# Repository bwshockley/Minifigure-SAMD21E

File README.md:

# Minifigure-SAMD21E
SAMD21E based Minifigure shaped development board.

## About
This circuit board was designed as a fun project for a SAMD21E microcontroller based development board.  The circuit design follows the recommended design from the SAMD Datasheet - including section 39. Schematic Checklist.  The USB protection may be overkill, but it is complete.  I made this just for fun - I am not going to provide any special support, but always welcome recommendations, suggestions, and ideas for improvements.  You are free to take it and run with it, but do not sell this design.

Order boards here:
Board 1: Stand alone - haven't tested, but should soon. [OSHPark](https://oshpark.com/shared_projects/Wh7NwFnv)

Board 2: This does not have a native USB or programming port - I am developing a backpack for it.  Will share backpack. [OSHPark](https://oshpark.com/shared_projects/W2bUXtFr)

MINI SAM TQFP SIMPLE - This version is more friendly to hand soldering with a TQFP SAMD21E chip.  USB protection and filtering removed, reset debounce removed.  [OSHPARK](https://oshpark.com/shared_projects/yFTXsDW0)

MINI SAM TQFP 1.27 SIMPLE - This version retains the TQFP SAMD21E chip, but on the back instead of the tiny 8-pin connector - I've replaced it with a 1.27mm pitch SMT connector.  Still trying to retain a "backpack" idea for add-on boards.  [OSHPARK](https://oshpark.com/shared_projects/vt6FGicv)

MINI SAM TQFP 2.54 BB (BreadBoard or Protoboard) - This version changes the rear once more to a 2.54mm pitch SMT setup for a protoboard friendly design. [OSHPARK](https://oshpark.com/shared_projects/SMD5UkUu)

Mini SAM - Protoboard - TQFP - 2017-01-17-00 - This version is similar to the other BB version, but has some refinements to layout and includes options for the onboard LED (Basic LED or the WS2812B), a plain button, and other enhancements.  [OSHPARK](https://oshpark.com/shared_projects/IhRoccbe)

Mini SAM 2017/01-001 - Latest version with minor changes and enhancements.  Once this version passes validation and verification, I will most likely archive other versions.  Details on [OSHPARK](https://oshpark.com/shared_projects/dv4tvRPH) and [here](https://github.com/bwshockley/Minifigure-SAMD21E/tree/master/board/2017/01).

----------------------------------

## Etc
The board passes all DRC for OSHPark manufacturing and should pass for most other manufacturers as well - I kept most routes, vias, etc larger than minimums and allowed plenty of space where I could.  I have tested many of these boards and all features work as designed.

## BOM
*The BOM listed at mouser is for the Mini SAM - Protoboard - TQFP - 2017-01-17-004 board.  It is a good place to start, but keep in mind you may want to change or leave out items you don't want.*

The schematic has all items listed and values and should be easily sourced.  Additionally, I have setup a [project on mouser.com that can be found here.](http://www.mouser.com/ProjectManager/ProjectDetail.aspx?AccessID=328cc4307e)  The BOM through mouser is roughly 12 USD at this time (Oct 2016).  It does not include the WS8212B 3535 LED - these can be sourced from [Adafruit](https://www.adafruit.com/products/2659) or eBay among others.  The LED does not need to be populated for the board to function, but it is fun.

## Firmware
I plan on trying to implement both Arduino and possibly Micropython on this board, but need some significant help with this.  I will update as I can.

In order to test my prototype board, I loaded the Arduino Zero bootloader, but changes the PortA pin 14 for PostA Pin 27.  Nothing else is fucntional yet - it was a bad hack to get access to the WS2812 LED for the time being and to prove to myself the board will work in theory.

(01-20-2017) FIRMWARE has been updated and almost complete.  I'm working through the last bit of verification and validation now.  Firmware and Arduino files are available in the arduino folder.  In order to burn the bootloader, the Atmel SAM-BA In-System Programmer must be installed first.

## License
Hardware - CC BY-NC 4.0 - See License file.

Software
Copyright (c) 2017 Benjamin Shockley

Permission is hereby granted, free of charge, to any person obtaining a copy
of this software and associated documentation files (the "Software"), to deal
in the Software without restriction, including without limitation the rights
to use, copy, modify, merge, publish, distribute, sublicense, and/or sell
copies of the Software, and to permit persons to whom the Software is
furnished to do so, subject to the following conditions:

The above copyright notice and this permission notice shall be included in all
copies or substantial portions of the Software.

THE SOFTWARE IS PROVIDED "AS IS", WITHOUT WARRANTY OF ANY KIND, EXPRESS OR
IMPLIED, INCLUDING BUT NOT LIMITED TO THE WARRANTIES OF MERCHANTABILITY,
FITNESS FOR A PARTICULAR PURPOSE AND NONINFRINGEMENT. IN NO EVENT SHALL THE
AUTHORS OR COPYRIGHT HOLDERS BE LIABLE FOR ANY CLAIM, DAMAGES OR OTHER
LIABILITY, WHETHER IN AN ACTION OF CONTRACT, TORT OR OTHERWISE, ARISING FROM,
OUT OF OR IN CONNECTION WITH THE SOFTWARE OR THE USE OR OTHER DEALINGS IN THE
SOFTWARE.

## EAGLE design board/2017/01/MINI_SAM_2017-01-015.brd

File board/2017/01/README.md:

##Board 2017/01-002

This is a LEGO Minifigure sized development board using an Atmel SAMD21E 32-Bit ARM chip. I basically followed the recommended layout/setup from the SAMD21 spec sheets.

Included on Mini SAM is a WS2812B LED (STATUS) connected to PIN 27, a 0603 LED (L) connected to PIN 15, a reset button (SW1) with circuitry per datasheet connected to !RESET, and a user programmable button (SW1) that is active HIGH connected to PIN 28. The 0603 LED is connected in series with a 1Kohm resistor, part of R1, and care should be taken when selecting an 0603 LED such that at a supply of 3.3V, no more than 5mA is required.

Programming port (PROG) is a basic 10-pin SWD for ARM based processors, which is a 2x5 1.27mm pitch connector. The SWD line is pulled up with a 1Kohm resistor, part of R1.

The SDA/SCL pins are pulled high with 4.7KOhm resistors, R2, per SDA/SCL recommendations.

The voltage regulator is an MCP1700 (IC1) which is rated at 250mA at 3.3V. Plenty of current for the SAMD21E and a few other accessories such as the WS2812B.

This version has SMT layout for two single row 2.54mm pitch headers on the back. It is designed to be protoboard friendly and when populated the headers are the same width as a DIL package (7.62mm or .3") and span the center of a protoboard.

PINs 27 and 28 are not connected to the headers - due to lack of space - but instead have two pads near the bottom of the board. Reminder: PIN 27 is connected to the on-board WS2812B and PIN 28 is connected to the on-board BUTTON.

The AREF PIN - PIN AREF - has a pair of decoupling/filtering capacitors (C6, C11).

The micro-USB connector has an RC filter (R6, C13) between the case/shield of the connector and GND. If left un-populated the case/shield is an open circuit - which is the next best option. Also included is space for a USBLC6-2 (IC2) ESD protection circuit. You can bypass it by jumping PAD 1 to 6, and PAD 3 to 4, leaving the middle two PADs alone of the layout for IC2.

I have put together a sample BOM via Mouser.com which I’m including here. It can be used as a reference. Items that do not need to be populated to work: SW2812B 3535 LED, 0603 LED, SW2 (BUTTON). The SW2812B is not in the Mouser BOM - due to lack of parts. I would suggest not purchasing the 2.54mm pitch SMT male headers from Mouser, as you can find this much cheaper elsewhere. Mini SAM requires (2) 11-PIN headers. I suggest buying breakaway headers in 25-50 PIN lengths.

Arduino FIRMWARE/BOOTLOADER is complete, but I’m still testing all functions. So far all PINs work in digital setup and all analog PINs work accordingly. ANALOG and special function pins (MOSI, SDA, SCK, etc) can be accessed in Arduino by their name.

##Board 2017/01-010

This is a LEGO Minifigure sized development board using an Atmel SAMD21E 32-Bit ARM chip.  I basically followed the recommended layout/setup from the SAMD21 spec sheets.

Included on Mini SAM is a WS2812B LED pad connected to PIN 27, a 0603 LED connected to PIN 15, a reset button with support components per the datasheet, and a generic button that is active HIGH on PIN 28. The 0603 LED is connected in series with a 1Kohm resistor, part of R1, and care should be taken when selecting an 0603 LED such that at a supply of 3.3V, no more than 5mA is required.

Programming port is a standard10-pin SWD for ARM based processors, which is a 2x5 1.27mm pitch connector.  The SWD line is pulled up with a 1Kohm resistor, part of R1.  In the BOM, either purchase the 2x5 straight pin connector OR the 2x5 POGO connector and do not populate board.

The SDA/SCL pins are pulled high with 4.7KOhm resistors, R2, per SDA/SCL recommendations.

The voltage regulator is an AP2112K-3.3V which is rated at 600mA at 3.3V.  Plenty of current for the SAMD21E and a few other accessories such as the WS2812B.

This version has SMT layout for two single row 2.54mm pitch headers on the back.  It is designed to be protoboard friendly and when populated the headers are the same width as a DIL package (7.62mm or .3") and span the center of a protoboard.

PINs 27 and 28 are not connected to headers - due to lack of space - but instead have two pads near the bottom of the board.  PIN 27 is connected to the on-board WS2812B.  PIN 28 is connected to the on-board BUTTON.

The Analog Reference (PIN AREF) - has a pair of decoupling/filtering capacitors.

The micro-USB connector has an RC filter between the case/shield of the connector and GND.  If R6 and C13 are left un-populated the case/shield is an open circuit - which is the next best option.  Also included is space for a PRTR5V0U2X ESD protection circuit on USB Data lines.  This may also be left un-populated and USB will function normally.

I have put together a sample BOM via Mouser.com which I'm including here.  It can be used as a reference.  Optional, but highly recommended components: SW2812B 3535 LED, 0603 LED, SW2 (BUTTON), R4, R5, R6, C13, and PRTR5V0U2X.  R1 is for the 0603 LED and SWCLK - If not populating the 0603 LED this *may* be left un-populated as well and programming via SWD should still work as I've seen other boards without the 1Kohm resistor on SWCLK.  R2 is the 4.7Kohm pull-up resistor pair for SDA/SCL.  Many breakout boards using chips that run off SDA/SCL typically come with the 4.7Kohm pull-up resistor pair included - as such it may not be needed on Mini SAM - but it is included for ease of future components.  Please review the schematic for additional details and be aware that the BOM on Mouser.com may be out of date.  *The SW2812B is not in the Mouser BOM - due to lack of parts.*

[Mouser BOM](http://www.mouser.com/ProjectManager/ProjectDetail.aspx?AccessID=fc486f90dc)

I would suggest not purchasing the 2.54mm pitch SMT male headers from Mouser, as you can find this much cheaper elsewhere.  The best I could find on Mouser is (2) 5-Pin and (2) 6-Pin headers.  Mini SAM requires (2) 11-PIN headers.  I suggest buying breakaway headers in 25-50 PIN lengths.

Arduino FIRMWARE/BOOTLOADER is complete, but I'm still testing all functions.  So far all PINs work in digital setup and all analog PINs work accordingly.  ANALOG and special function pins (MOSI, SDA, SCK, etc) can be accessed in Arduino by their name.

Please check my Github for the latest design files and bootloade/firmware.

More details can be found on [Github](https://github.com/bwshockley/Minifigure-SAMD21E)

##Board 2017/01-012
Same as 2017/01-010 with minor cosmetic changes.

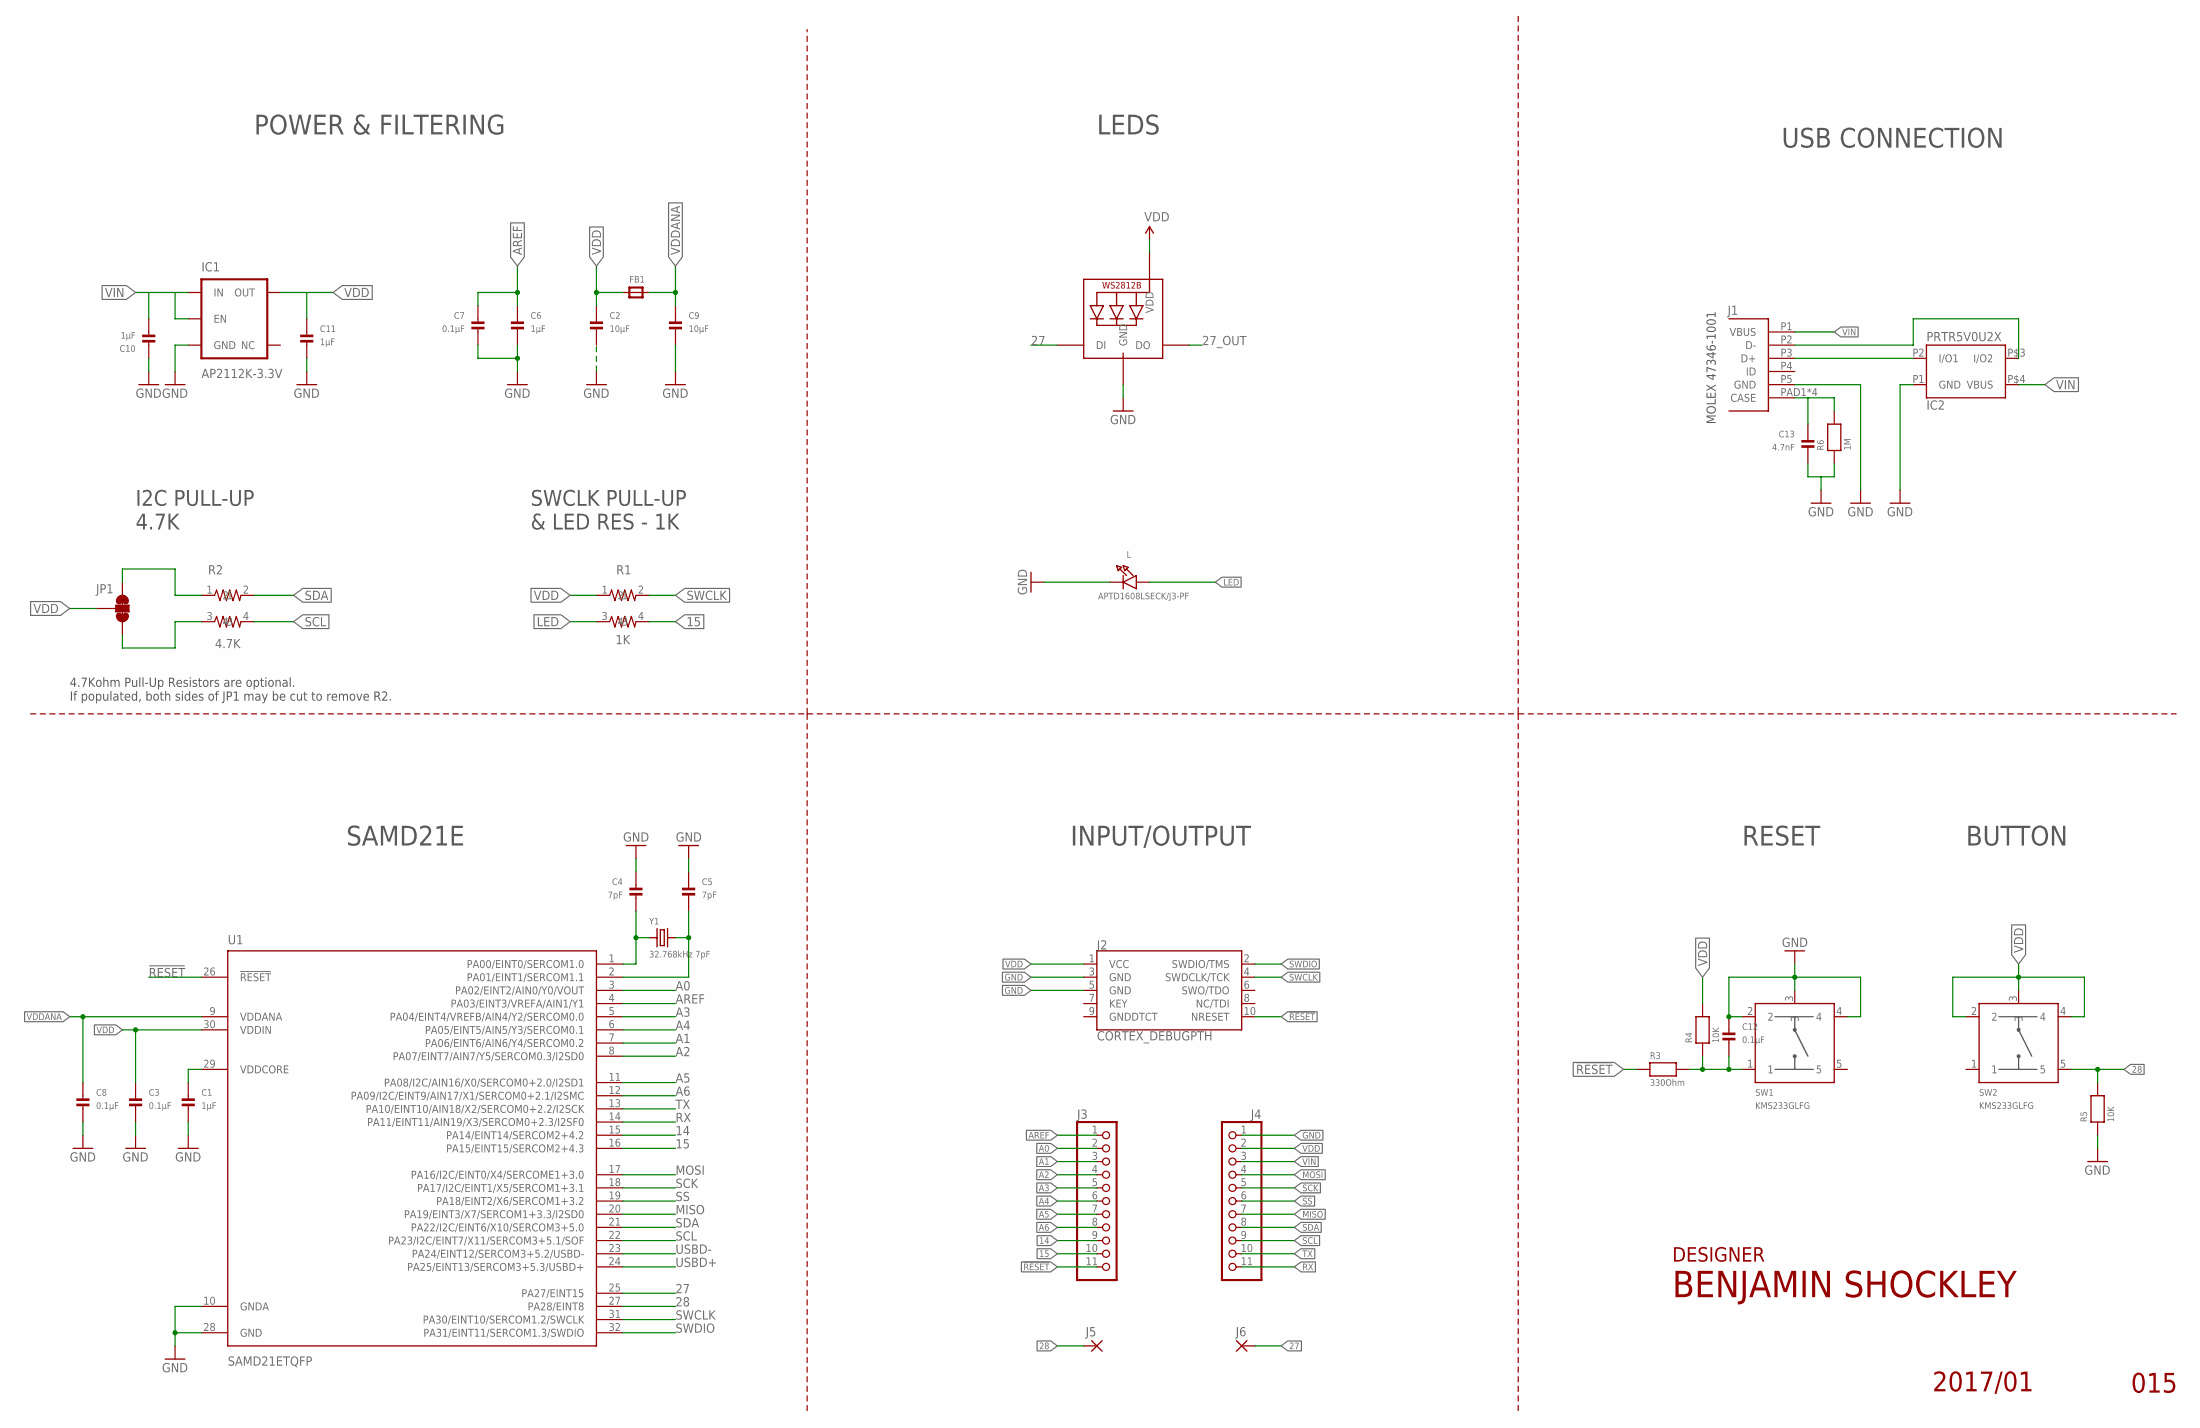
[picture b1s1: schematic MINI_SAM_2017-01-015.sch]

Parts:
C1, C6, C10, C11: 1µF; _0805MP
C2, C9: 10µF; _0805MP
C3, C7, C8, C12: 0.1µF; _0805MP
C4, C5: 7pF; _0805MP
C13: 4.7nF; _0805MP
FB1: FERRITE_0805MP; _0805MP
IC1: AP2112K-3.3V; SOT23-5
IC2: PRTR5V0U2X; SOT143B_REFLOW
J1: MOLEX_47346-100147346; MOLEX_47346-1001
J2: CORTEX_DEBUGPTH; 2X5-PTH-1.27MM
J3, J4: PINHD-1X111X11_SMT; 1X11_SMT
J5, J6: FR11_PAD2MMX1MM; SMD2MMX1MM
JP1: JUMPER-SMT_3_2-NC_TRACE_NO-SILK; SMT-JUMPER_3_2-NC_TRACE_NO-SILK
L: APTD1608LSECK/J3-PF; CHIPLED_0603_NOOUTLINE
R1: 1K; RESISTOR_ARRAY_0606
R2: 4.7K; RESISTOR_ARRAY_0606
R3: 330Ohm; _0805MP
R4, R5: 10K; _0805MP
R6: 1M; _0805MP
STATUS: WS2812B3535; LED3535
SW1, SW2: KMS233GLFG; KMS_SWITCH
U1: SAMD21ETQFP; TQFP32-08
Y1: 32.768kHz 7pF; _0805MP

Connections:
14: J3.9, U1.15 (PA14/EINT14/SERCOM2+4.2)
15: J3.10, R1.4, U1.16 (PA15/EINT15/SERCOM2+4.3)
27: J6.P$1, STATUS.1 (DI), U1.25 (PA27/EINT15)
27_OUT: STATUS.3 (DO)
28: J5.P$1, R5.2, SW2.5, U1.27 (PA28/EINT8)
!RESET: J2.10 (NRESET), J3.11, R3.1, U1.26 (!RESET)
A0: J3.2, U1.3 (PA02/EINT2/AIN0/Y0/VOUT)
A1: J3.3, U1.7 (PA06/EINT6/AIN6/Y4/SERCOM0.2)
A2: J3.4, U1.8 (PA07/EINT7/AIN7/Y5/SERCOM0.3/I2SD0)
A3: J3.5, U1.5 (PA04/EINT4/VREFB/AIN4/Y2/SERCOM0.0)
A4: J3.6, U1.6 (PA05/EINT5/AIN5/Y3/SERCOM0.1)
A5: J3.7, U1.11 (PA08/I2C/AIN16/X0/SERCOM0+2.0/I2SD1)
A6: J3.8, U1.12 (PA09/I2C/EINT9/AIN17/X1/SERCOM0+2.1/I2S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)
AREF: C6.1, C7.1, J3.1, U1.4 (PA03/EINT3/VREFA/AIN1/Y1)
GND: C1.2, C2.2, C3.2, C4.1, C5.1, C6.2, C7.2, C8.2, C9.2, C10.1, C11.2, C12.1, C13.2, IC1.2 (GND), IC2.P1 (GND), J1.P5 (GND), J2.3 (GND), J2.5 (GND), J4.1, L.C, R5.1, R6.1, STATUS.4 (GND), SW1.2, SW1.3, SW1.4, U1.10 (GNDA), U1.28 (GND)
LED: L.A, R1.3
MISO: J4.7, U1.20 (PA19/EINT3/X7/SERCOM1+3.3/I2SD0)
MOSI: J4.4, U1.17 (PA16/I2C/EINT0/X4/SERCOME1+3.0)
unnamed: C4.2, U1.1 (PA00/EINT0/SERCOM1.0), Y1.1
unnamed: C13.1, J1.PAD1 (CASE), J1.PAD2 (CASE), J1.PAD3 (CASE), J1.PAD4 (CASE), R6.2
unnamed: JP1.1, R2.1
unnamed: C12.2, R3.2, R4.1, SW1.1
unnamed: C5.2, U1.2 (PA01/EINT1/SERCOM1.1), Y1.2
unnamed: JP1.3, R2.3
unnamed: C1.1, U1.29 (VDDCORE)
RX: J4.11, U1.14 (PA11/EINT11/AIN19/X3/SERCOM0+2.3/I2SF0)
SCK: J4.5, U1.18 (PA17/I2C/EINT1/X5/SERCOM1+3.1)
SCL: J4.9, R2.4, U1.22 (PA23/I2C/EINT7/X11/SERCOM3+5.1/SOF)
SDA: J4.8, R2.2, U1.21 (PA22/I2C/EINT6/X10/SERCOM3+5.0)
SS: J4.6, U1.19 (PA18/EINT2/X6/SERCOM1+3.2)
SWCLK: J2.4 (SWDCLK/TCK), R1.2, U1.31 (PA30/EINT10/SERCOM1.2/SWCLK)
SWDIO: J2.2 (SWDIO/TMS), U1.32 (PA31/EINT11/SERCOM1.3/SWDIO)
TX: J4.10, U1.13 (PA10/EINT10/AIN18/X2/SERCOM0+2.2/I2SCK)
USBD+: IC2.P2 (I/O1), J1.P3 (D+), U1.24 (PA25/EINT13/SERCOM3+5.3/USBD+)
USBD-: IC2.P$3 (I/O2), J1.P2 (D-), U1.23 (PA24/EINT12/SERCOM3+5.2/USBD-)
VDD: C2.1, C3.1, C11.1, FB1.1, IC1.5 (OUT), J2.1 (VCC), J4.2, JP1.2, R1.1, R4.2, STATUS.2 (VDD), SW2.2, SW2.3, SW2.4, U1.30 (VDDIN)
VDDANA: C8.1, C9.1, FB1.2, U1.9 (VDDANA)
VIN: C10.2, IC1.1 (IN), IC1.3 (EN), IC2.P$4 (VBUS), J1.P1 (VBUS), J4.3

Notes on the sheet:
INPUT/OUTPUT
RESET
POWER & FILTERING
SAMD21E
LEDS
USB CONNECTION
I2C PULL-UP 4.7K
MOLEX 47346-1001
BUTTON
SWCLK PULL-UP & LED RES - 1K
DESIGNER
4.7Kohm Pull-Up Resistors are optional. If populated, both sides of JP1 may be cut to remove R2.

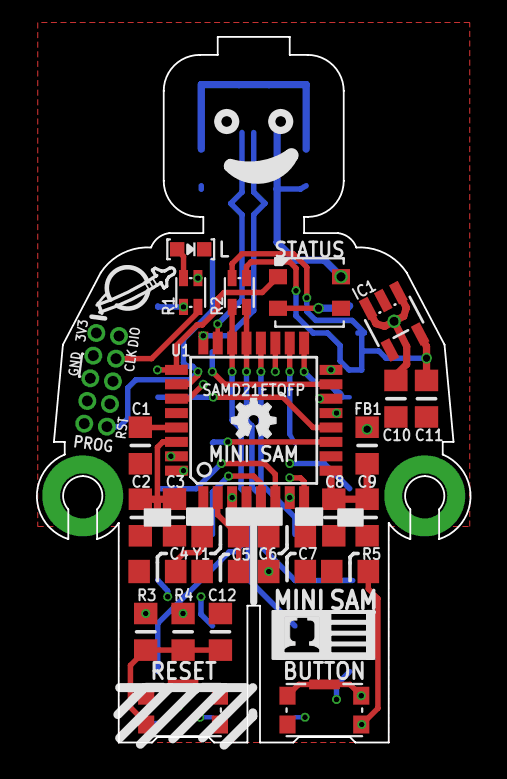
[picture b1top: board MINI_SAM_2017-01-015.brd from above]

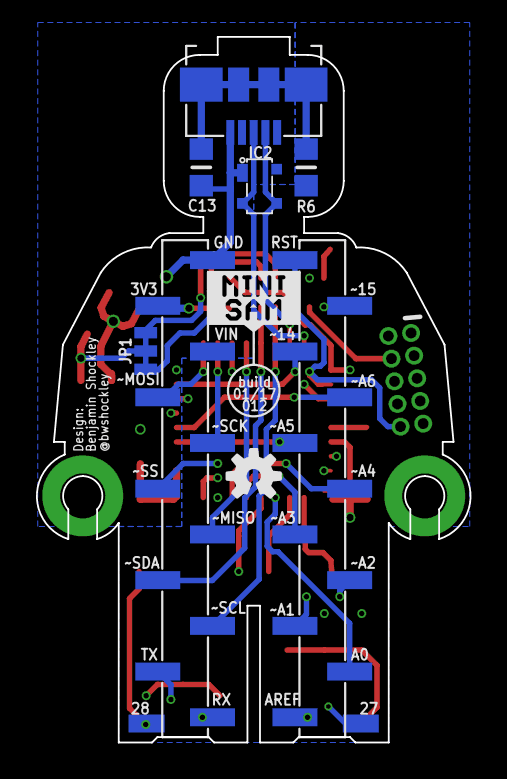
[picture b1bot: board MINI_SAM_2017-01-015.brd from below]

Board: 4 copper layers, 24.1 x 39.2 mm, 37 parts (10 on the bottom side), 37 nets.

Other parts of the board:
U$1: OSHW-LOGO-MINI
U$3: OSHW-LOGO-S

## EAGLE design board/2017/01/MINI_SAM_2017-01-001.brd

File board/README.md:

#EAGLE Files
At this time I only have EAGLE files for the Minifigure Board.  If someone wants to convert them to KiCAD, I'd be happy to add those files to the repository.

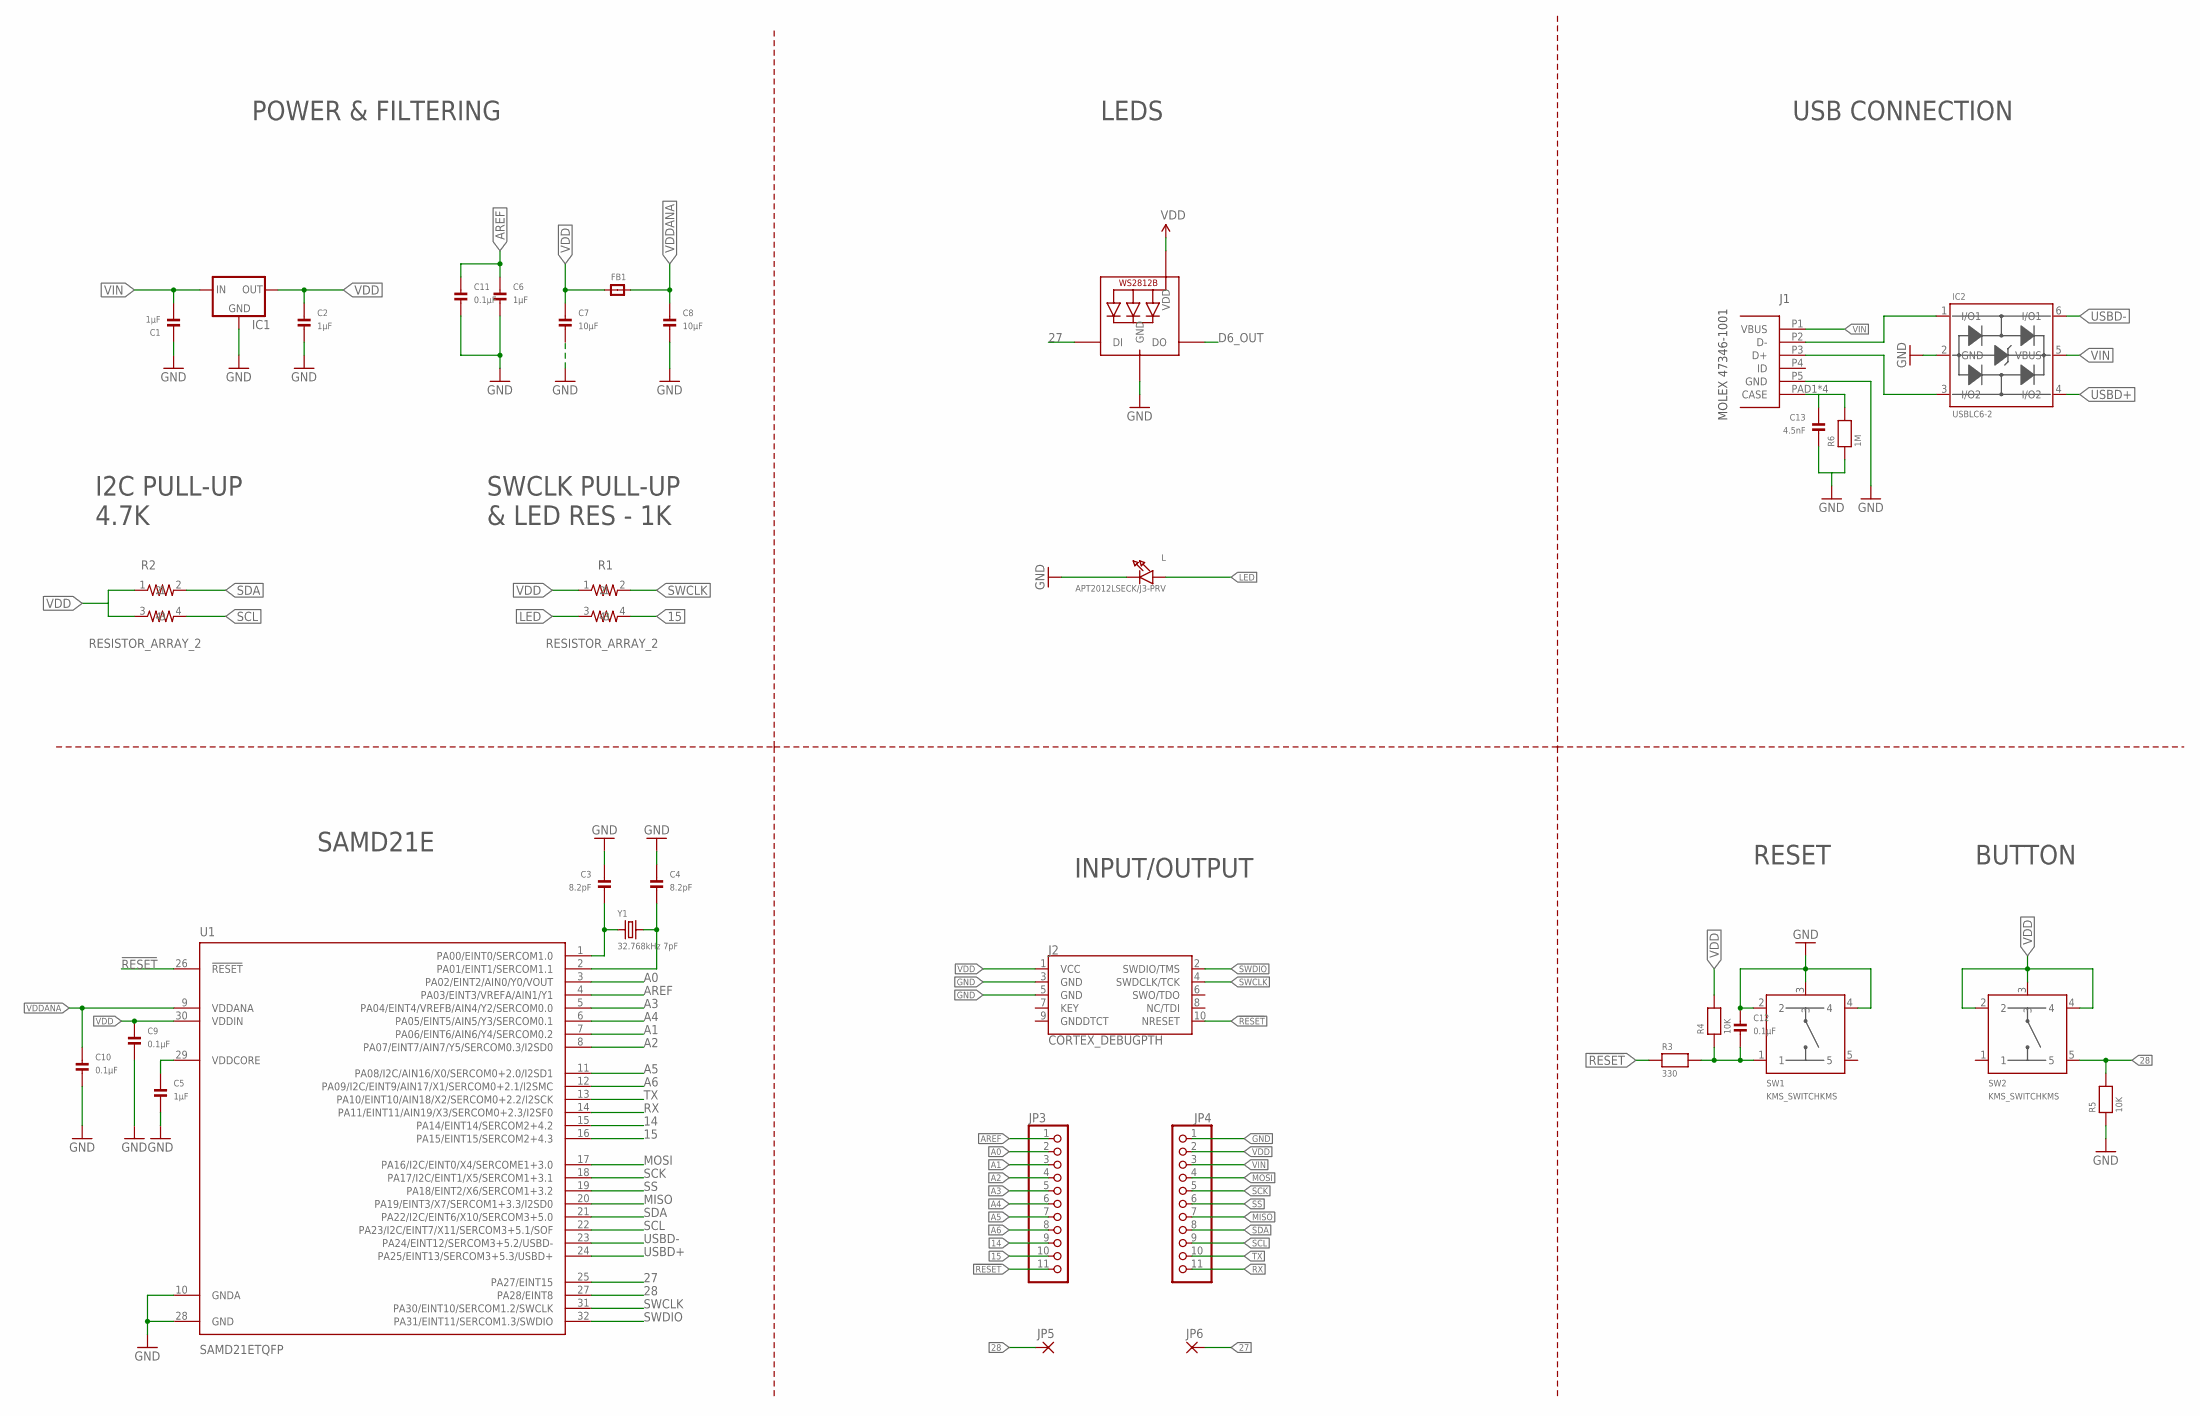
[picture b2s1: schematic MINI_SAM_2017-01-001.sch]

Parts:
C1, C2, C5, C6: 1µF; _0805MP
C3, C4: 8.2pF; _0805MP
C7, C8: 10µF; _0805MP
C9, C10, C11, C12: 0.1µF; _0805MP
C13: 4.5nF; _0805MP
FB1: FERRITE_0805MP; _0805MP
IC1: MCP1700; SOT23
IC2: USBLC6-2; SOT23-6L
J1: MOLEX_47346-100147346; MOLEX_47346-1001
J2: CORTEX_DEBUGPTH; 2X5-PTH-1.27MM
JP3, JP4: PINHD-1X111X11_SMT; 1X11_SMT
JP5, JP6: FR11_PAD2MMX1MM; SMD2MMX1MM
L: APT2012LSECK/J3-PRV; CHIPLED_0603_NOOUTLINE
R1, R2: RESISTOR_ARRAY_2; RESISTOR_ARRAY_0606
R3: 330; _0805MP
R4, R5: 10K; _0805MP
R6: 1M; _0805MP
STATUS: WS2812B3535; LED3535
SW1, SW2: KMS_SWITCHKMS; KMS_SWITCH
U1: SAMD21ETQFP; TQFP32-08
Y1: 32.768kHz 7pF; _0805MP

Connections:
14: JP3.9, U1.15 (PA14/EINT14/SERCOM2+4.2)
15: JP3.10, R1.4, U1.16 (PA15/EINT15/SERCOM2+4.3)
27: JP6.P$1, STATUS.1 (DI), U1.25 (PA27/EINT15)
28: JP5.P$1, R5.2, SW2.5, U1.27 (PA28/EINT8)
!RESET: J2.10 (NRESET), JP3.11, R3.1, U1.26 (!RESET)
A0: JP3.2, U1.3 (PA02/EINT2/AIN0/Y0/VOUT)
A1: JP3.3, U1.7 (PA06/EINT6/AIN6/Y4/SERCOM0.2)
A2: JP3.4, U1.8 (PA07/EINT7/AIN7/Y5/SERCOM0.3/I2SD0)
A3: JP3.5, U1.5 (PA04/EINT4/VREFB/AIN4/Y2/SERCOM0.0)
A4: JP3.6, U1.6 (PA05/EINT5/AIN5/Y3/SERCOM0.1)
A5: JP3.7, U1.11 (PA08/I2C/AIN16/X0/SERCOM0+2.0/I2SD1)
A6: JP3.8, U1.12 (PA09/I2C/EINT9/AIN17/X1/SERCOM0+2.1/I2S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)
AREF: C6.1, C11.1, JP3.1, U1.4 (PA03/EINT3/VREFA/AIN1/Y1)
D6_OUT: STATUS.3 (DO)
GND: C1.1, C2.2, C3.1, C4.1, C5.2, C6.2, C7.2, C8.2, C9.2, C10.2, C11.2, C12.1, C13.2, IC1.1 (GND), IC2.2 (GND), J1.P5 (GND), J2.3 (GND), J2.5 (GND), JP4.1, L.C, R5.1, R6.1, STATUS.4 (GND), SW1.2, SW1.3, SW1.4, U1.10 (GNDA), U1.28 (GND)
INUSBD+: IC2.3 (I/O2), J1.P3 (D+)
INUSBD-: IC2.1 (I/O1), J1.P2 (D-)
LED: L.A, R1.3
MISO: JP4.7, U1.20 (PA19/EINT3/X7/SERCOM1+3.3/I2SD0)
MOSI: JP4.4, U1.17 (PA16/I2C/EINT0/X4/SERCOME1+3.0)
unnamed: C3.2, U1.1 (PA00/EINT0/SERCOM1.0), Y1.1
unnamed: C13.1, J1.PAD1 (CASE), J1.PAD2 (CASE), J1.PAD3 (CASE), J1.PAD4 (CASE), R6.2
unnamed: C12.2, R3.2, R4.1, SW1.1
unnamed: C4.2, U1.2 (PA01/EINT1/SERCOM1.1), Y1.2
unnamed: C5.1, U1.29 (VDDCORE)
RX: JP4.11, U1.14 (PA11/EINT11/AIN19/X3/SERCOM0+2.3/I2SF0)
SCK: JP4.5, U1.18 (PA17/I2C/EINT1/X5/SERCOM1+3.1)
SCL: JP4.9, R2.4, U1.22 (PA23/I2C/EINT7/X11/SERCOM3+5.1/SOF)
SDA: JP4.8, R2.2, U1.21 (PA22/I2C/EINT6/X10/SERCOM3+5.0)
SS: JP4.6, U1.19 (PA18/EINT2/X6/SERCOM1+3.2)
SWCLK: J2.4 (SWDCLK/TCK), R1.2, U1.31 (PA30/EINT10/SERCOM1.2/SWCLK)
SWDIO: J2.2 (SWDIO/TMS), U1.32 (PA31/EINT11/SERCOM1.3/SWDIO)
TX: JP4.10, U1.13 (PA10/EINT10/AIN18/X2/SERCOM0+2.2/I2SCK)
USBD+: IC2.4 (I/O2), U1.24 (PA25/EINT13/SERCOM3+5.3/USBD+)
USBD-: IC2.6 (I/O1), U1.23 (PA24/EINT12/SERCOM3+5.2/USBD-)
VDD: C2.1, C7.1, C9.1, FB1.1, IC1.2 (OUT), J2.1 (VCC), JP4.2, R1.1, R2.1, R2.3, R4.2, STATUS.2 (VDD), SW2.2, SW2.3, SW2.4, U1.30 (VDDIN)
VDDANA: C8.1, C10.1, FB1.2, U1.9 (VDDANA)
VIN: C1.2, IC1.3 (IN), IC2.5 (VBUS), J1.P1 (VBUS), JP4.3

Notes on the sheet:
INPUT/OUTPUT
RESET
POWER & FILTERING
SAMD21E
LEDS
USB CONNECTION
I2C PULL-UP 4.7K
MOLEX 47346-1001
BUTTON
SWCLK PULL-UP & LED RES - 1K

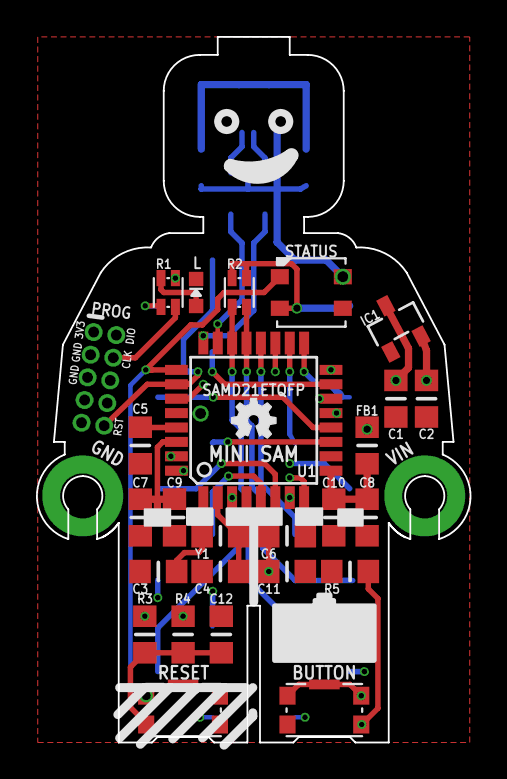
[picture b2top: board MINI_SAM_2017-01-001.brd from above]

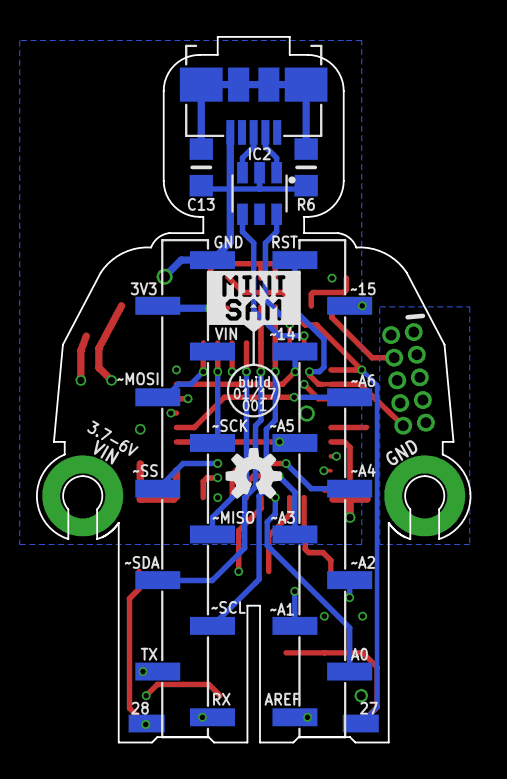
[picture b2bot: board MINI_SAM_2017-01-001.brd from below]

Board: 4 copper layers, 24.1 x 39.2 mm, 36 parts (9 on the bottom side), 37 nets.

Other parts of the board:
U$1: OSHW-LOGO-MINI
U$3: OSHW-LOGO-S

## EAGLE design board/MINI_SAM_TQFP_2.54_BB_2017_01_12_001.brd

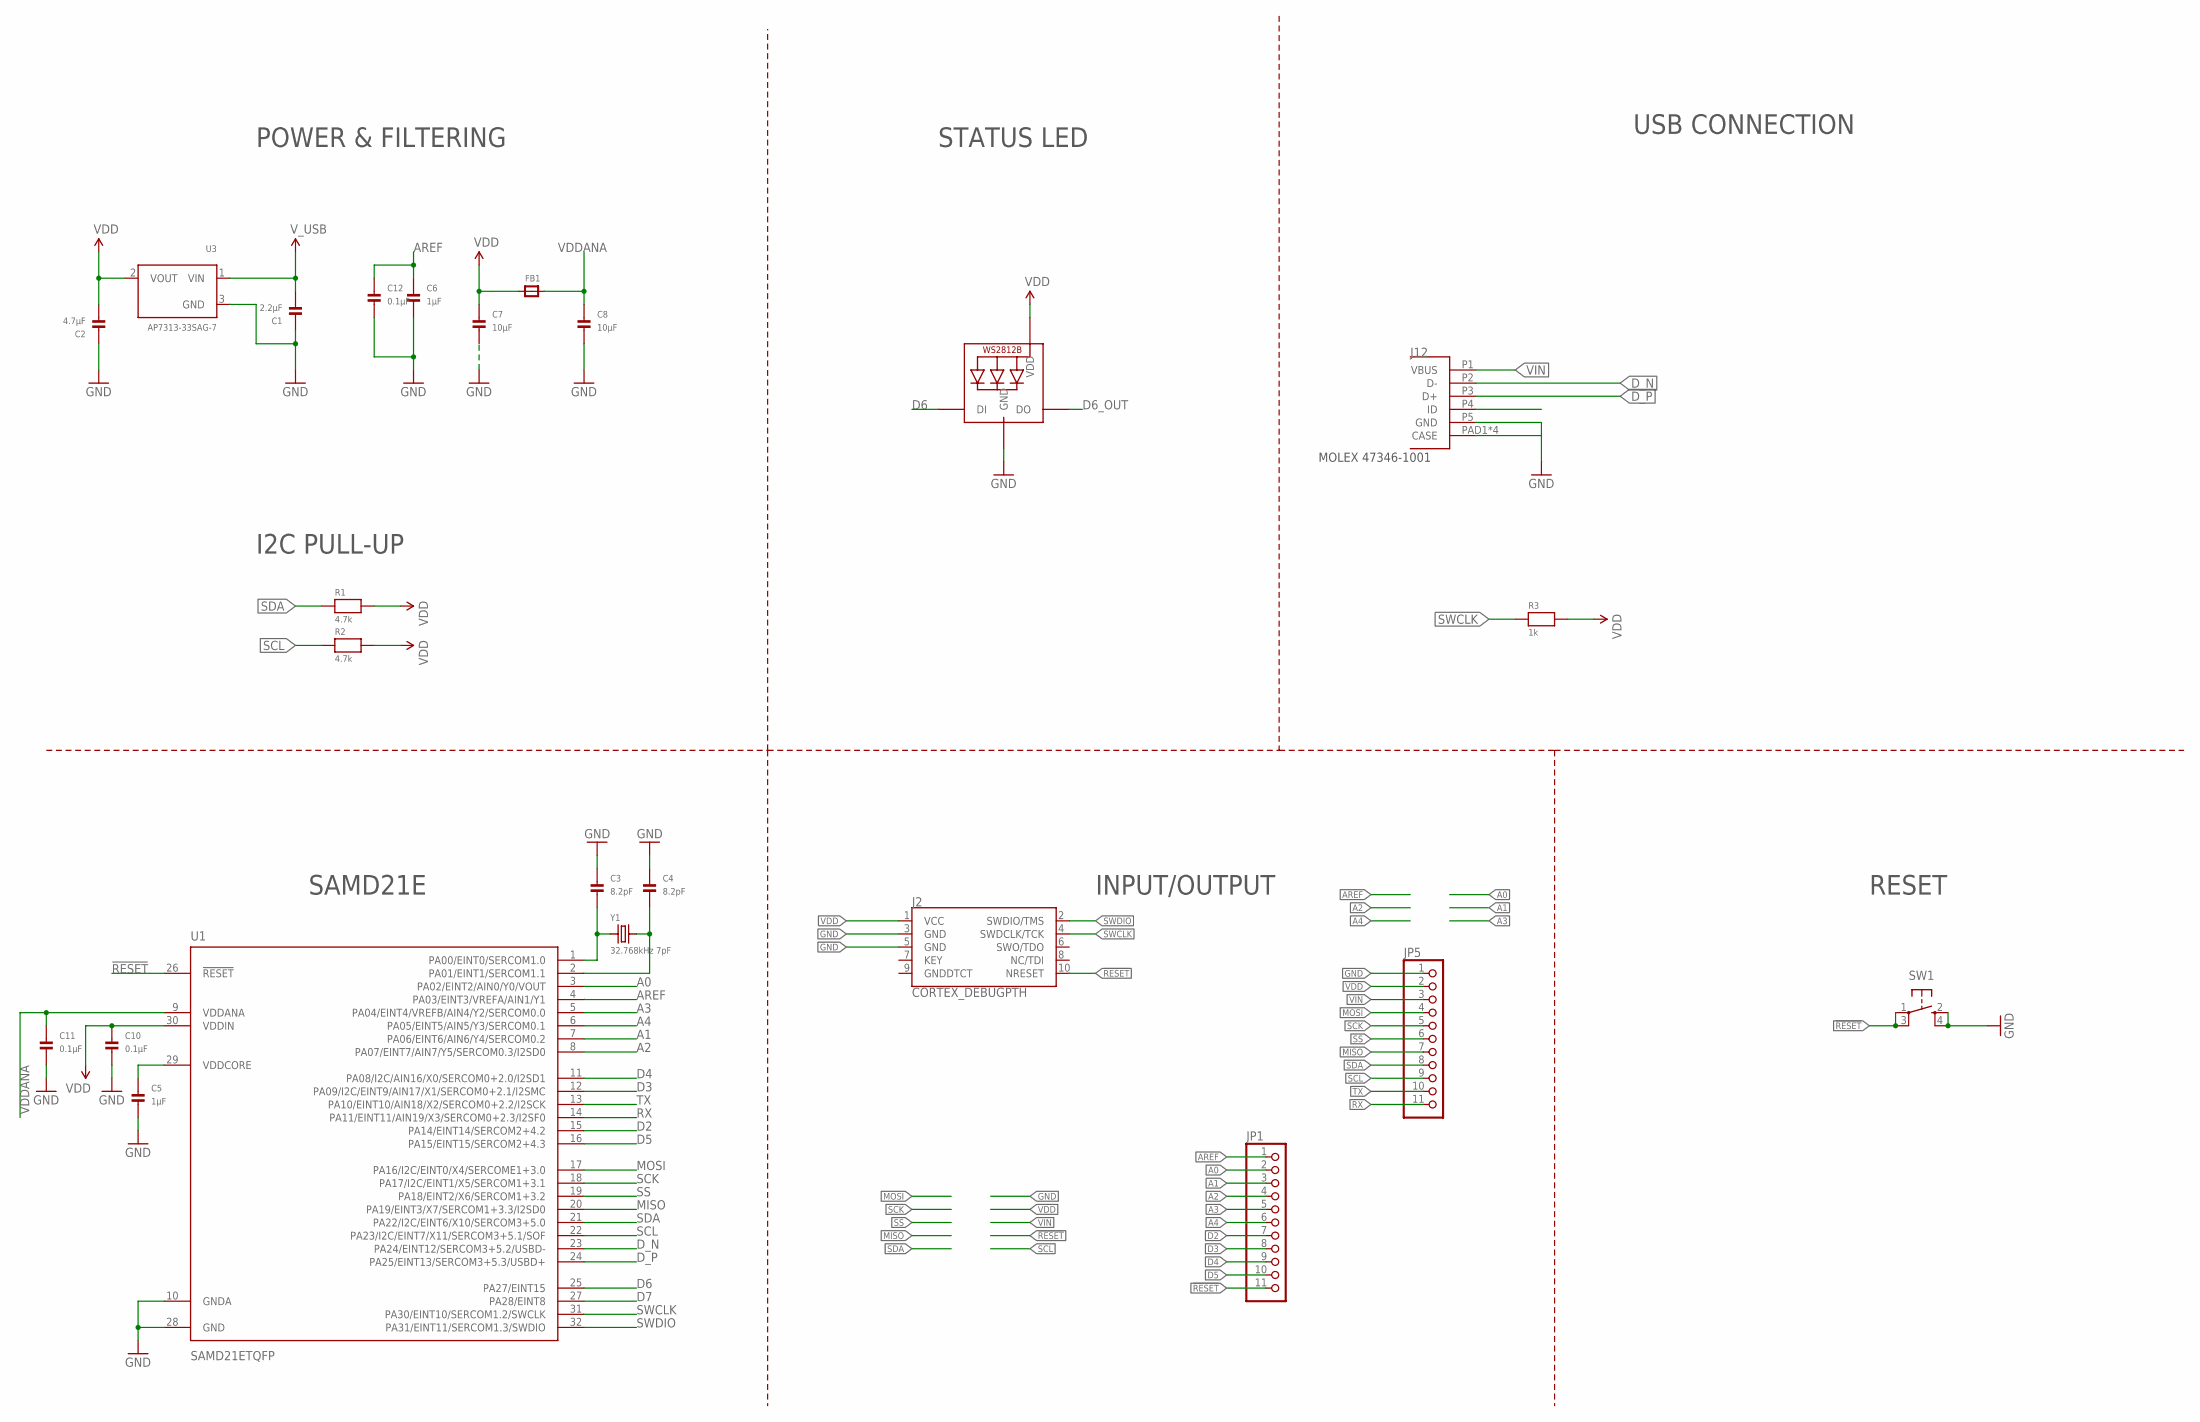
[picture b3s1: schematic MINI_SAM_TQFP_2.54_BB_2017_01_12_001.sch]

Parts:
C1: 2.2µF; _0805MP
C2: 4.7µF; _0805MP
C3, C4: 8.2pF; _0805MP
C5, C6: 1µF; _0805MP
C7, C8: 10µF; _0805MP
C10, C11, C12: 0.1µF; _0805MP
FB1: FERRITE_0805MP; _0805MP
J2: CORTEX_DEBUGPTH; 2X5-PTH-1.27MM
J12: MOLEX_47346-100147346; MOLEX_47346-1001
JP1, JP5: PINHD-1X111X11_SMT; 1X11_SMT
R1, R2: 4.7k; _0805MP
R3: 1k; _0805MP
STATUS: WS2812B3535; LED3535
SW1: SPST_TACT-KMR2; KMR2
U1: SAMD21ETQFP; TQFP32-08
U3: AP7313-33SAG-7; SOT23-R
Y1: 32.768kHz 7pF; _0805MP

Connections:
!RESET: J2.10 (NRESET), JP1.11, SW1.1, SW1.3 (P1), U1.26 (!RESET)
A0: JP1.2, U1.3 (PA02/EINT2/AIN0/Y0/VOUT)
A1: JP1.3, U1.7 (PA06/EINT6/AIN6/Y4/SERCOM0.2)
A2: JP1.4, U1.8 (PA07/EINT7/AIN7/Y5/SERCOM0.3/I2SD0)
A3: JP1.5, U1.5 (PA04/EINT4/VREFB/AIN4/Y2/SERCOM0.0)
A4: JP1.6, U1.6 (PA05/EINT5/AIN5/Y3/SERCOM0.1)
AREF: C6.1, C12.1, JP1.1, U1.4 (PA03/EINT3/VREFA/AIN1/Y1)
D2: JP1.7, U1.15 (PA14/EINT14/SERCOM2+4.2)
D3: JP1.8, U1.12 (PA09/I2C/EINT9/AIN17/X1/SERCOM0+2.1/I2S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)
D4: JP1.9, U1.11 (PA08/I2C/AIN16/X0/SERCOM0+2.0/I2SD1)
D5: JP1.10, U1.16 (PA15/EINT15/SERCOM2+4.3)
D6: STATUS.1 (DI), U1.25 (PA27/EINT15)
D6_OUT: STATUS.3 (DO)
D7: U1.27 (PA28/EINT8)
D_N: J12.P2 (D-), U1.23 (PA24/EINT12/SERCOM3+5.2/USBD-)
D_P: J12.P3 (D+), U1.24 (PA25/EINT13/SERCOM3+5.3/USBD+)
GND: C1.1, C2.1, C3.1, C4.1, C5.2, C6.2, C7.2, C8.2, C10.2, C11.2, C12.2, J2.3 (GND), J2.5 (GND), J12.P5 (GND), J12.PAD1 (CASE), J12.PAD2 (CASE), J12.PAD3 (CASE), J12.PAD4 (CASE), JP5.1, STATUS.4 (GND), SW1.2 (S), SW1.4 (S1), U1.10 (GNDA), U1.28 (GND), U3.3 (GND)
MISO: JP5.7, U1.20 (PA19/EINT3/X7/SERCOM1+3.3/I2SD0)
MOSI: JP5.4, U1.17 (PA16/I2C/EINT0/X4/SERCOME1+3.0)
unnamed: C3.2, U1.1 (PA00/EINT0/SERCOM1.0), Y1.1
unnamed: C4.2, U1.2 (PA01/EINT1/SERCOM1.1), Y1.2
unnamed: C5.1, U1.29 (VDDCORE)
RX: JP5.11, U1.14 (PA11/EINT11/AIN19/X3/SERCOM0+2.3/I2SF0)
SCK: JP5.5, U1.18 (PA17/I2C/EINT1/X5/SERCOM1+3.1)
SCL: JP5.9, R2.1, U1.22 (PA23/I2C/EINT7/X11/SERCOM3+5.1/SOF)
SDA: JP5.8, R1.1, U1.21 (PA22/I2C/EINT6/X10/SERCOM3+5.0)
SS: JP5.6, U1.19 (PA18/EINT2/X6/SERCOM1+3.2)
SWCLK: J2.4 (SWDCLK/TCK), R3.1, U1.31 (PA30/EINT10/SERCOM1.2/SWCLK)
SWDIO: J2.2 (SWDIO/TMS), U1.32 (PA31/EINT11/SERCOM1.3/SWDIO)
TX: JP5.10, U1.13 (PA10/EINT10/AIN18/X2/SERCOM0+2.2/I2SCK)
VDD: C2.2, C7.1, C10.1, FB1.1, J2.1 (VCC), JP5.2, R1.2, R2.2, R3.2, STATUS.2 (VDD), U1.30 (VDDIN), U3.2 (VOUT)
VDDANA: C8.1, C11.1, FB1.2, U1.9 (VDDANA)
VIN: C1.2, J12.P1 (VBUS), JP5.3, U3.1 (VIN)

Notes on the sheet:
INPUT/OUTPUT
RESET
POWER & FILTERING
SAMD21E
STATUS LED
USB CONNECTION
I2C PULL-UP
MOLEX 47346-1001

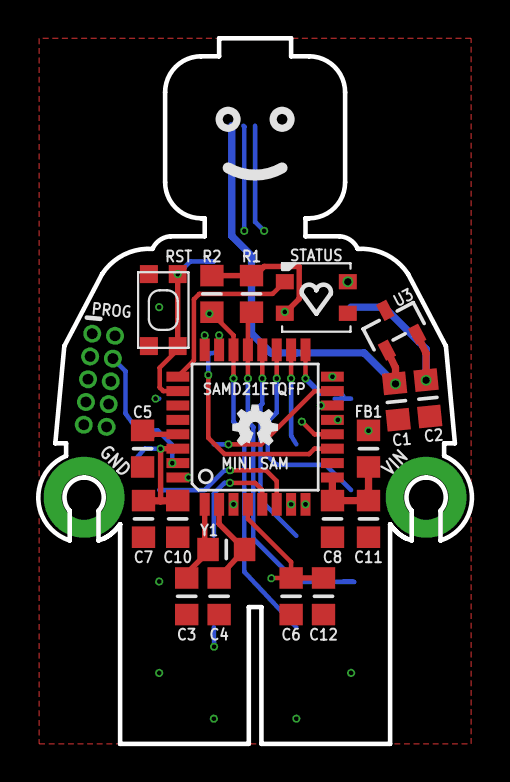
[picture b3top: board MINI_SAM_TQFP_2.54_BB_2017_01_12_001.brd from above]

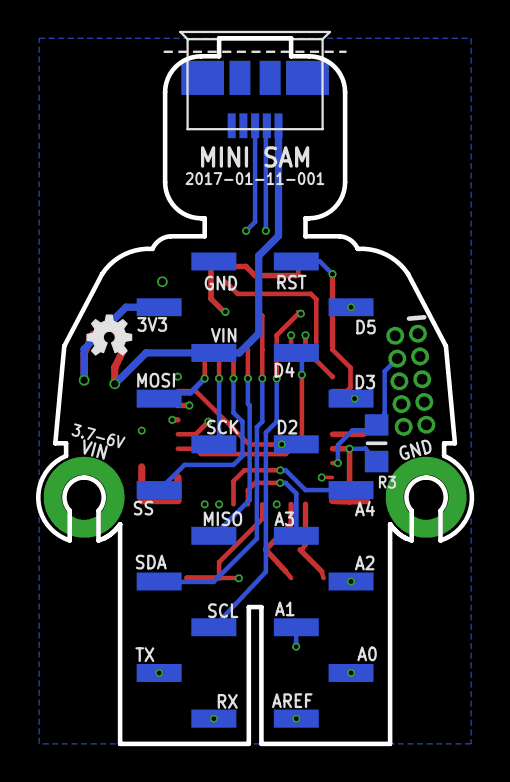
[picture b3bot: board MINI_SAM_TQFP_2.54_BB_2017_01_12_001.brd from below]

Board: 4 copper layers, 24.1 x 39.2 mm, 26 parts (5 on the bottom side), 31 nets.

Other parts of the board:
U$1, U$2: OSHW-LOGO-MINI

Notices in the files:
arduino/mini_sam/hardware/samd/1.0.0/variants/mini_sam/variant.cpp:
Copyright (c) 2014-2015 Arduino LLC.  All right reserved.
parts and their libraries:
microbuilder: This work is placed in the public domain, and may be freely used for commercial and non-commercial work with the following conditions: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
SparkFun-Aesthetics: Licensing: Creative Commons ShareAlike 4.0 International - https://creativecommons.org/licenses/by-sa/4.0
